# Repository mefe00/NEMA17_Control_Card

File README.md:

# STM32G tabanlı NEMA17 sürücü kartı 

> Bu proje, NEMA17 gibi step motorları alanın az olduğu yerlerde hem kompakt boyut sağlamak hemde kablo karmaşını en aza indirmek için tasarlanmıştır.

## 📋 Özellikler

* MCU: STM32G431CBT6
* Çalışma Gerilimi: 24V
* Haberleşme: CAN/CAN-FD: Kartta iki tane CAN konnektörü vardır. Bu sayede aynı karta veya aynı CAN hattı üzerindeki başka bir kartla haberleşmek için bir konnektöre giriş yapıp diğer konnektörden çıkabilirsiniz ve diğer cihaza giriş yapabilirsiniz. Dikkat: Eğer kartı CAN                   hattının son cihazı ise 60 ohmları buna uygun bir şekilde montajlayın !!!!
              I2C: Eğer motorda redüktör varsa ve kartın arkasındaki encoder kullanılmak istenmezse harici ucuz bir encoder (AS5600) girişi redüktör ucundan alınması içindir. Diğer amacı ise yine bir encoder bağlayıp redüktör boşluğu (backlash) tespiti yapılabilmesi içindir.
              USART: Debug veya direkt haberleşme sağlanabilmesi için. 
* Koruma: 26V seviyesini aşarsa sürücü koruması için TVS diyot
* Encoder: AS5147-P ----> Kartın direkt arkasında bulunur ve pahalı ve kaliteli seçilmesinin sebebi ise redüktör eklenen motorlarda milin daha hızlı dönmesinden dolayı açı verisinin kaçmasını engellemek içindir.
           AS5600   ----> Karta harici bir şekilde girilebilir. Kart üzerinde bunun için harici I2C konnektörü vardır.
* NTC: Kart üzerindeki sıcaklığı tespit etmek için kullanılabilir.
* FAN: NTC'den alınan verilere göre veya manuel soğutma için 24V fan desteği vardır.
* Sürücü: TMC2209 seçilmiştir ama TMC2208 veya pinleri uyuşan başka bir sürücüde kullanılabilir. 

## 📂 Depo İçeriği

* `/Hardware`: KiCAD şematik (`.kicad_sch`) ve PCB (`.kicad_pcb`) tasarım dosyaları.
* `/production`: Üretime hazır Gerber ve Drill dosyaları.
* `/software`: Kartın robot kol eksenlerindeki motorları kontrolü için hazırlanmış gömülü kodu.

## Tavsiyeler

* Güç girişine 50V / 1000uF seviyelerinde bir elektrolit kapasitör eklenmesi.
* Sürücülerin bozulması durumları düşünüldüğü için modül olarak yerleştirilmiştir ve modulün altı boş olduğu için burayada 50V / 220uF seviyelerinde elektrolit kapasitör eklenmesi.
* Daha kararlı bir çalışma olabilmesi için sürücü üzerine soğutucu (heatsink) yerleştirin.
* Daha soğuk bir çalışma için soğutu bloğu buck converter üzerinede yerleştirebilirsiniz.

## Diğer Görseller

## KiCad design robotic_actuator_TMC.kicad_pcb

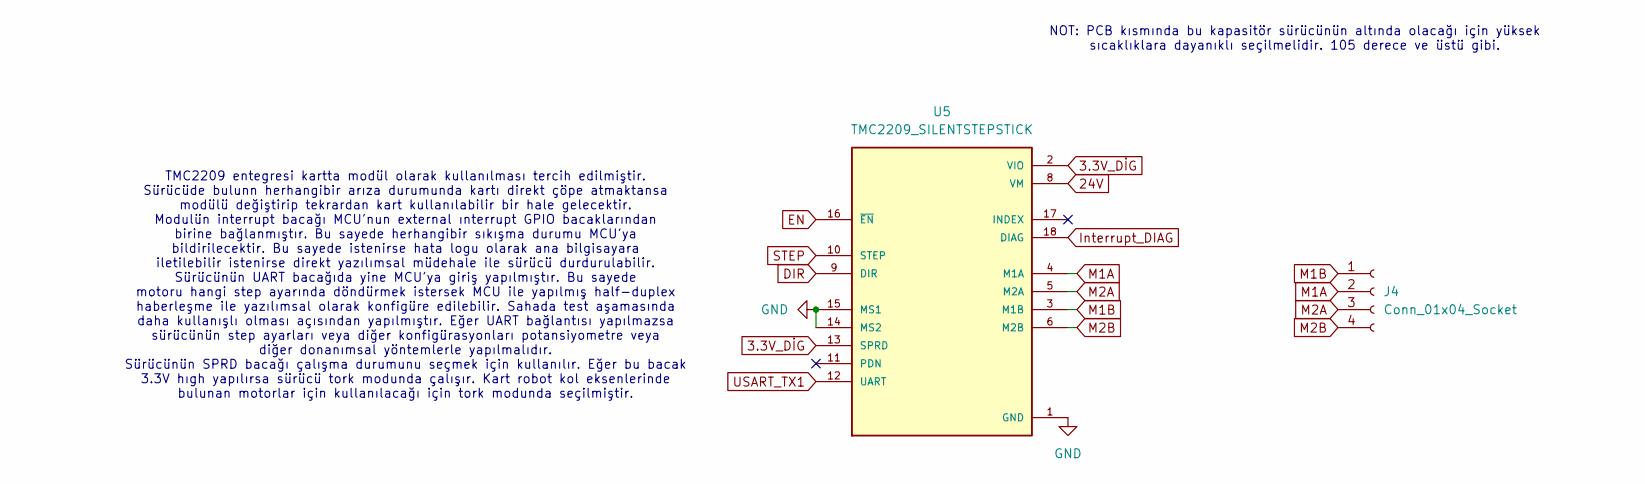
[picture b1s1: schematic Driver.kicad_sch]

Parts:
J4: Conn_01x04_Socket; JST_PH_S4B-PH-K_1x04_P2.00mm_Horizontal
U5: TMC2209_SILENTSTEPSTICK; MODULE_TMC2209_SILENTSTEPSTICK; PARTREV 1.20

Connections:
3.3V_DİG: U5.2 (VIO), U5.13 (SPRD); also elsewhere on the board
24V: U5.8 (VM); also elsewhere on the board
DIR: U5.9 (DIR); also elsewhere on the board
EN: U5.16 (~EN); also elsewhere on the board
GND: U5.1 (GND), U5.7 (GND), U5.14 (MS2), U5.15 (MS1); also elsewhere on the board
Interrupt_DIAG: U5.18 (DIAG); also elsewhere on the board
M1A: J4.2, U5.4 (M1A)
M1B: J4.1, U5.3 (M1B)
M2A: J4.3, U5.5 (M2A)
M2B: J4.4, U5.6 (M2B)
STEP: U5.10 (STEP); also elsewhere on the board
USART_TX1: U5.12 (UART); also elsewhere on the board

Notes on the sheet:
TMC2209 entegresi kartta modül olarak kullanılması tercih edilmiştir. Sürücüde bulunn herhangibir arıza durumunda kartı direkt çöpe atmaktansa modülü değiştirip tekrardan kart kullanılabilir bir hale gelecektir. Modulün interrupt bacağı MCU'nun external ınterrupt GPIO bacaklarından birine bağlanmış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
NOT: PCB kısmında bu kapasitör sürücünün altında olacağı için yüksek sıcaklıklara dayanıklı seçilmelidir. 105 derece ve üstü gibi.

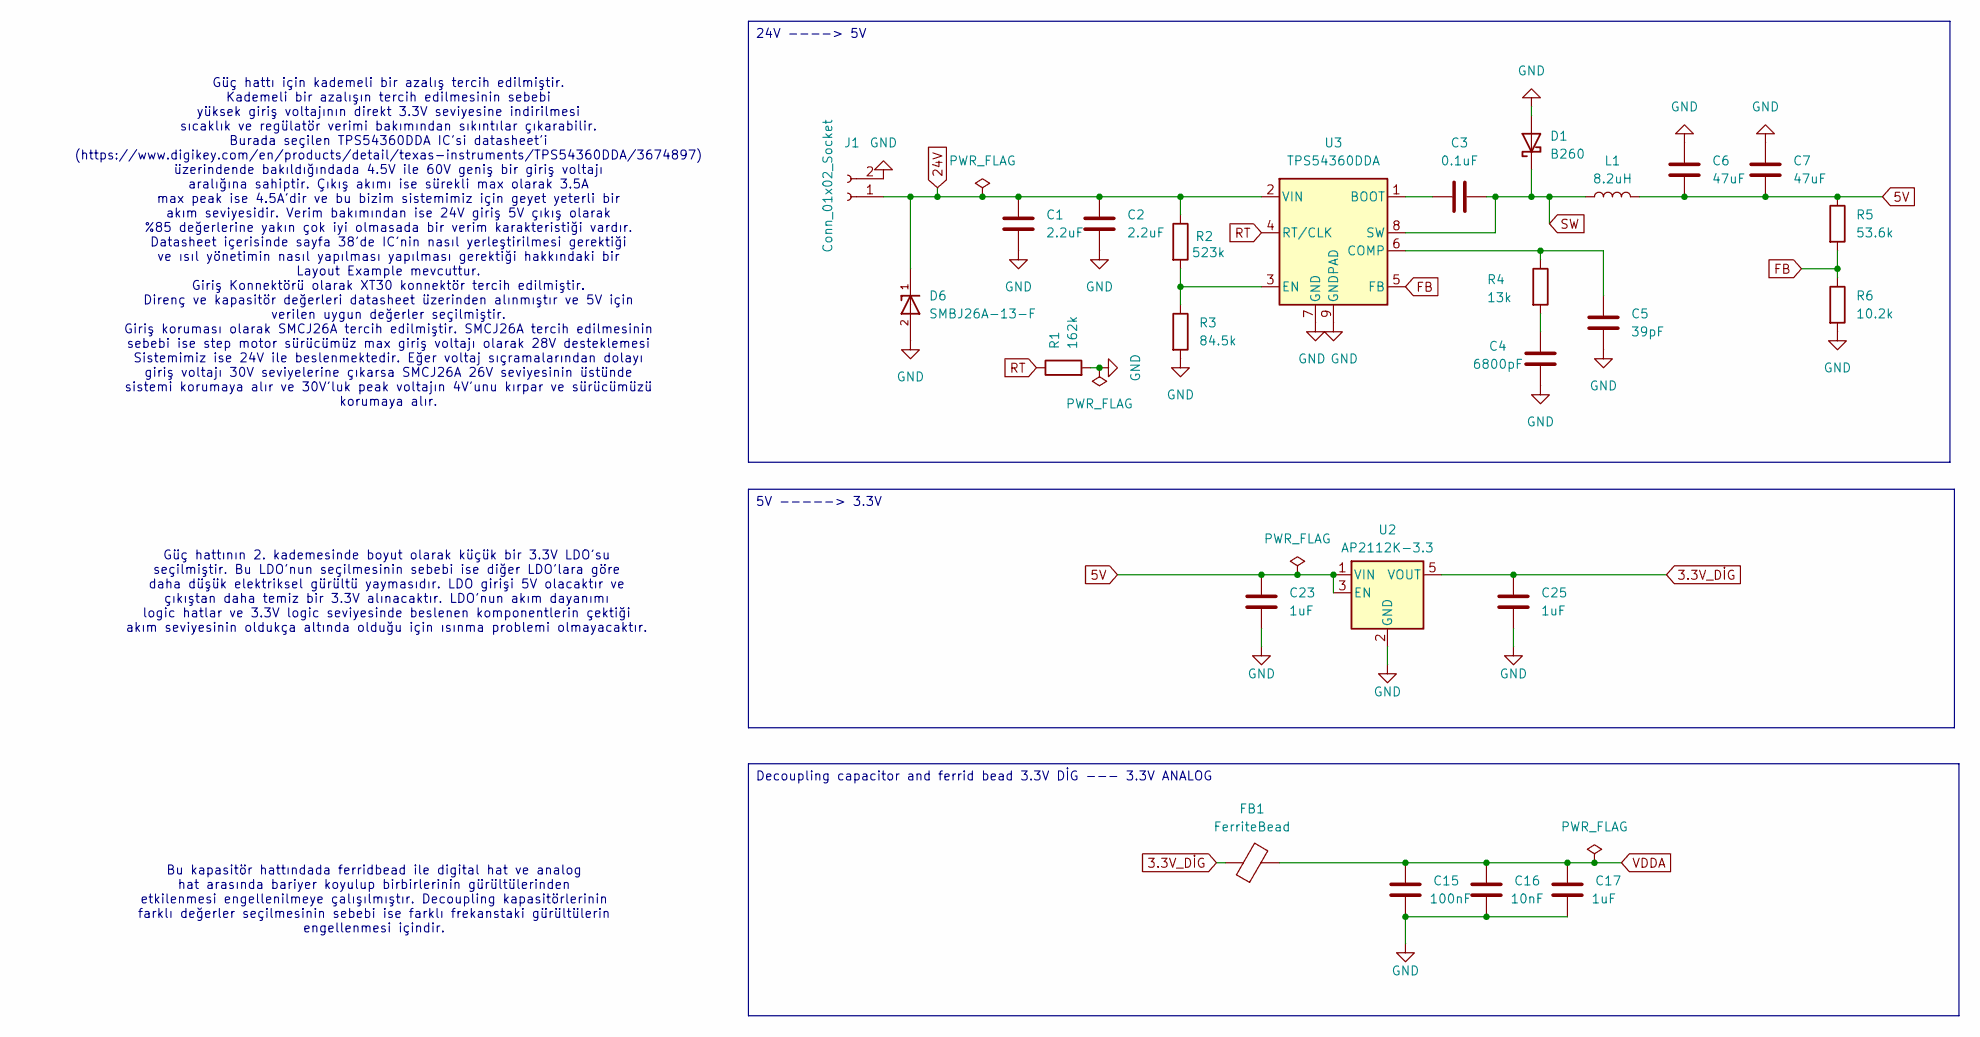
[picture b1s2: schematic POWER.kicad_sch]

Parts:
C1, C2: 2.2uF; C_1206_3216Metric
C3: 0.1uF; C_0603_1608Metric
C4: 6800pF; C_0603_1608Metric
C5: 39pF; C_0603_1608Metric
C6, C7: 47uF; C_0805_2012Metric
C15: 100nF; C_0603_1608Metric
C16: 10nF; C_0603_1608Metric
C17, C23, C25: 1uF; C_0603_1608Metric
D1: B260; D_SMA
D6: SMBJ26A-13-F; D_SMB; PARTREV 20 - 2
FB1: FerriteBead; L_0603_1608Metric
J1: Conn_01x02_Socket; AMASS_XT30U-F_1x02_P5.0mm_Vertical
L1: 8.2uH; L_6.3x6.3_H3
R1: 162k; R_0603_1608Metric
R2: 523k; R_0603_1608Metric
R3: 84.5k; R_0603_1608Metric
R4: 13k; R_0603_1608Metric
R5: 53.6k; R_0603_1608Metric
R6: 10.2k; R_0603_1608Metric
U2: AP2112K-3.3; SOT-23-5
U3: TPS54360DDA; TI_SO-PowerPAD-8_ThermalVias

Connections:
3.3V_DİG: C25.1, FB1.1, U2.5 (VOUT); also elsewhere on the board
5V: C6.1, C7.1, C23.1, L1.2, R5.1, U2.1 (VIN), U2.3 (EN); also elsewhere on the board
24V: C1.1, C2.1, D6.1, J1.1, R2.1, U3.2 (VIN); also elsewhere on the board
FB: R5.2, R6.1, U3.5 (FB)
GND: C1.2, C2.2, C4.1, C5.1, C6.2, C7.2, C15.2, C16.2, C17.2, C23.2, C25.2, D1.2 (A), D6.2, J1.2, R1.2, R3.2, R6.2, U2.2 (GND), U3.7 (GND), U3.9 (GNDPAD); also elsewhere on the board
unnamed: C4.2, R4.2
unnamed: C3.1, U3.1 (BOOT)
unnamed: C5.2, R4.1, U3.6 (COMP)
unnamed: R2.2, R3.1, U3.3 (EN)
RT: R1.1, U3.4 (RT/CLK)
SW: C3.2, D1.1 (K), L1.1, U3.8 (SW)
VDDA: C15.1, C16.1, C17.1, FB1.2; also elsewhere on the board

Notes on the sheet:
Güç hattının 2. kademesinde boyut olarak küçük bir 3.3V LDO'su seçilmiştir. Bu LDO'nun seçilmesinin sebebi ise diğer LDO'lara göre daha düşük elektriksel gürültü yaymasıdır. LDO girişi 5V olacaktır ve çıkıştan daha temiz bir 3.3V alınacaktır. LDO'nun akım dayanımı logic hatlar ve 3.3V logic seviyes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
Bu kapasitör hattındada ferridbead ile digital hat ve analog hat arasında bariyer koyulup birbirlerinin gürültülerinden etkilenmesi engellenilmeye çalışılmıştır. Decoupling kapasitörlerinin farklı değerler seçilmesinin sebebi ise farklı frekanstaki gürültülerin engellenmesi içindir.
Güç hattı için kademeli bir azalış tercih edilmiştir. Kademeli bir azalışın tercih edilmesinin sebebi yüksek giriş voltajının direkt 3.3V seviyesine indirilmesi sıcaklık ve regülatör verimi bakımından sıkıntılar çıkarabilir. Burada seçilen TPS54360DDA IC'si datasheet'i (https://www.digikey.com/en/p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
Decoupling capacitor and ferrid bead 3.3V DİG --- 3.3V ANALOG
5V -----> 3.3V
24V ----> 5V

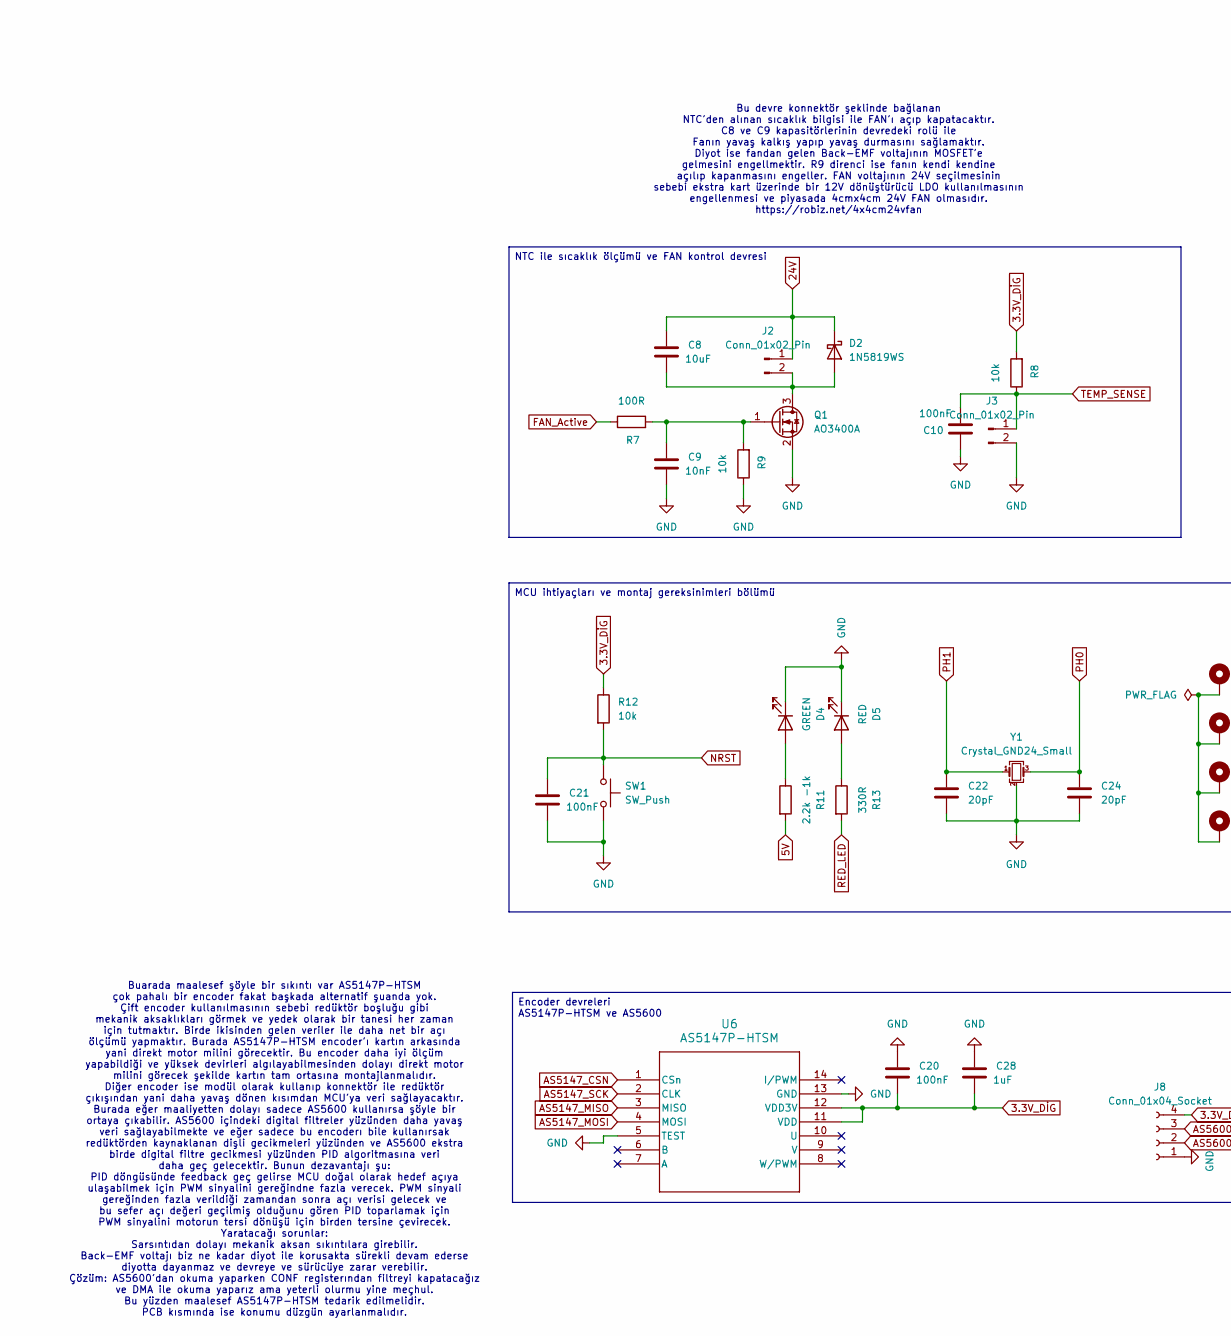
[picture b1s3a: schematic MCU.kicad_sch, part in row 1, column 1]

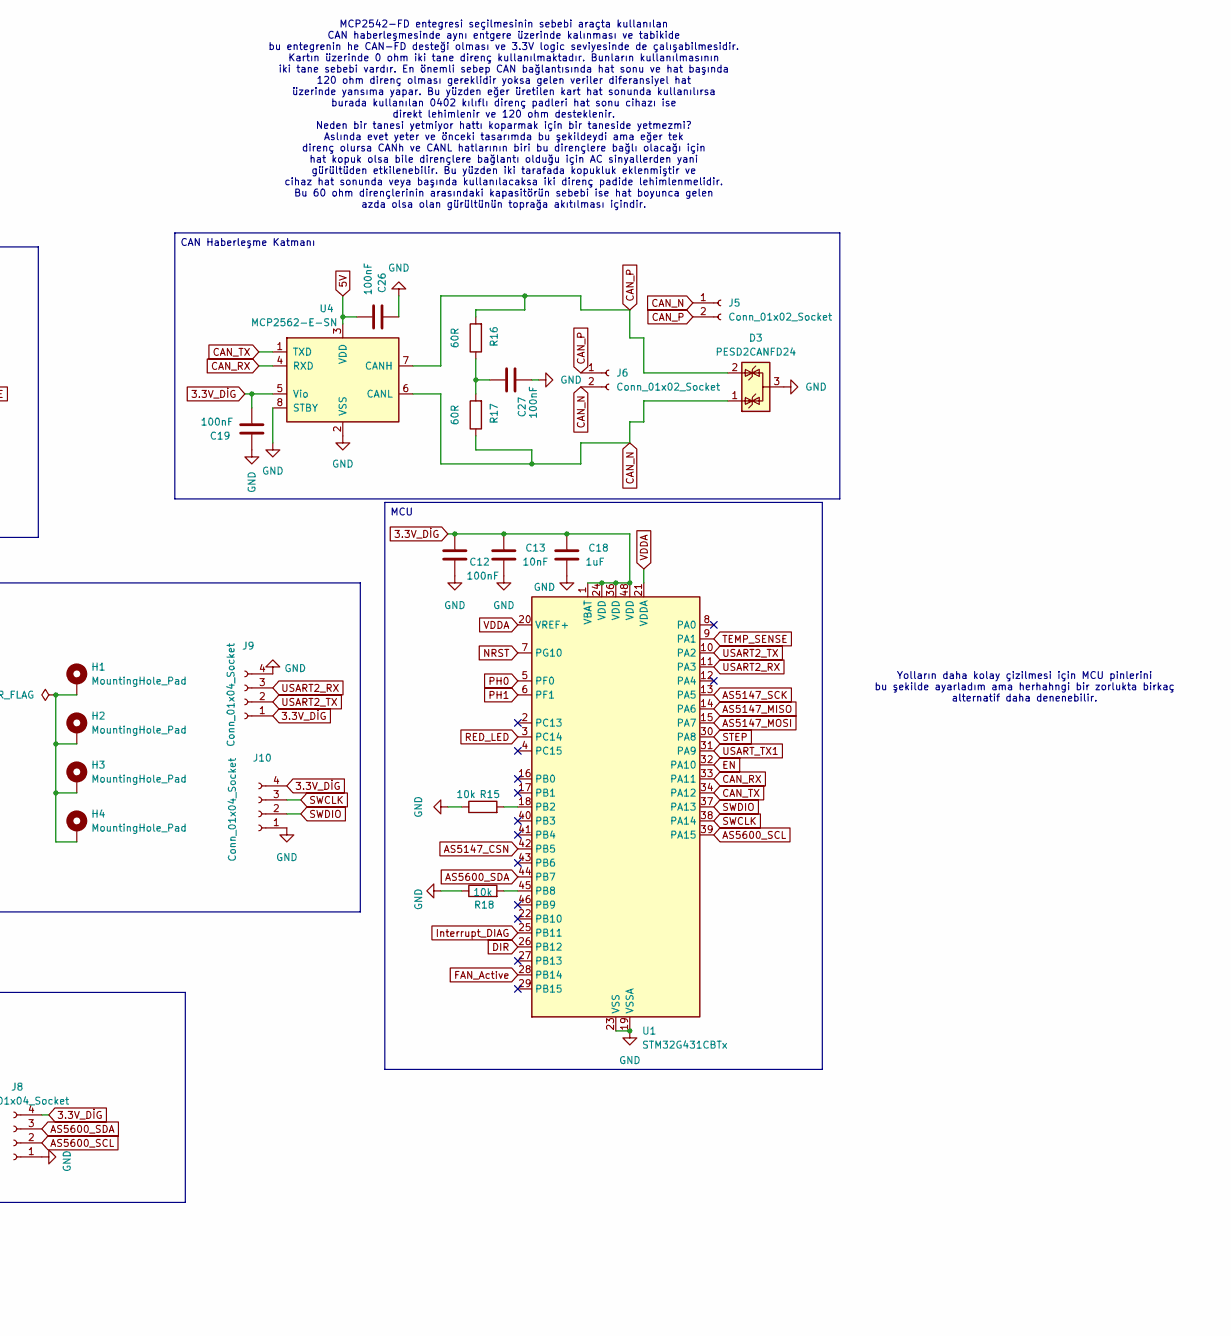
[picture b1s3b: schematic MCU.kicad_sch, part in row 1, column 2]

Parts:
C8: 10uF; C_0603_1608Metric
C9, C13: 10nF; C_0603_1608Metric
C10, C12, C19, C20, C21, C26, C27: 100nF; C_0603_1608Metric
C18, C28: 1uF; C_0603_1608Metric
C22, C24: 20pF; C_0603_1608Metric
D2: 1N5819WS; D_SOD-323
D3: PESD2CANFD24; DIO_PESD2CAN_215
D4: GREEN; LED_0603_1608Metric
D5: RED; LED_0603_1608Metric
H1, H2, H3, H4: MountingHole_Pad; MountingHole_3.5mm
J2, J3: Conn_01x02_Pin; PinHeader_1x02_P2.54mm_Vertical
J5, J6: Conn_01x02_Socket; JST_GH_SM02B-GHS-TB_1x02-1MP_P1.25mm_Horizontal
J8, J9, J10: Conn_01x04_Socket; JST_GH_SM04B-GHS-TB_1x04-1MP_P1.25mm_Horizontal
Q1: AO3400A; SOT-23
R7: 100R; R_0603_1608Metric
R8, R9, R12, R15, R18: 10k; R_0603_1608Metric
R11: 2.2k -1k; R_0603_1608Metric
R13: 330R; R_0603_1608Metric
R16, R17: 60R; R_0603_1608Metric
SW1: SW_Push; SW_Push_1P1T_NO_CK_KMR2
U1: STM32G431CBTx; LQFP-48_7x7mm_P0.5mm
U4: MCP2562-E-SN; SOIC-8_3.9x4.9mm_P1.27mm
U6: AS5147P-HTSM; TSSOP-14_AMS
Y1: Crystal_GND24_Small; Crystal_SMD_3225-4Pin_3.2x2.5mm

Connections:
3.3V_DİG: C12.1, C13.1, C18.1, C19.2, C20.2, C28.2, J8.4, J9.1, J10.4, R8.2, R12.1, U1.1 (VBAT), U1.24 (VDD), U1.36 (VDD), U1.48 (VDD), U4.5 (Vio), U6.11 (VDD), U6.12 (VDD3V); also elsewhere on the board
5V: C26.2, R11.2, U4.3 (VDD); also elsewhere on the board
24V: C8.1, D2.1 (K), J2.1; also elsewhere on the board
AS5147_CSN: U1.42 (PB5), U6.1 (CSn)
AS5147_MISO: U1.14 (PA6), U6.3 (MISO)
AS5147_MOSI: U1.15 (PA7), U6.4 (MOSI)
AS5147_SCK: U1.13 (PA5), U6.2 (CLK)
AS5600_SCL: J8.2, U1.39 (PA15)
AS5600_SDA: J8.3, U1.44 (PB7)
CAN_N: D3.1 (K), J5.1, J6.2, R17.1, U4.6 (CANL)
CAN_P: D3.2 (K), J5.2, J6.1, R16.2, U4.7 (CANH)
CAN_RX: U1.33 (PA11), U4.4 (RXD)
CAN_TX: U1.34 (PA12), U4.1 (TXD)
DIR: U1.26 (PB12); also elsewhere on the board
EN: U1.32 (PA10); also elsewhere on the board
FAN_Active: R7.1, U1.28 (PB14)
GND: C9.2, C10.2, C12.2, C13.2, C18.2, C19.1, C20.1, C21.2, C22.2, C24.2, C26.1, C27.2, C28.1, D3.3 (A), D4.1 (K), D5.1 (K), J3.2, J8.1, J9.4, J10.1, Q1.2 (S), R9.1, R15.1, R18.1, SW1.2, U1.19 (VSSA), U1.23 (VSS), U1.35 (VSS), U1.47 (VSS), U4.2 (VSS), U4.8 (STBY), U6.5 (TEST), U6.13 (GND), Y1.2 (G), Y1.4 (G); also elsewhere on the board
Interrupt_DIAG: U1.25 (PB11); also elsewhere on the board
NRST: C21.1, R12.2, SW1.1, U1.7 (PG10)
unnamed: C27.1, R16.1, R17.2
unnamed: C8.2, D2.2 (A), J2.2, Q1.3 (D)
unnamed: D4.2 (A), R11.1
unnamed: D5.2 (A), R13.1
unnamed: C9.1, Q1.1 (G), R7.2, R9.2
unnamed: R15.2, U1.18 (PB2)
unnamed: R18.2, U1.45 (PB8)
PH0: C24.1, U1.5 (PF0), Y1.3
PH1: C22.1, U1.6 (PF1), Y1.1
RED_LED: R13.2, U1.3 (PC14)
STEP: U1.30 (PA8); also elsewhere on the board
SWCLK: J10.3, U1.38 (PA14)
SWDIO: J10.2, U1.37 (PA13)
TEMP_SENSE: C10.1, J3.1, R8.1, U1.9 (PA1)
USART2_RX: J9.3, U1.11 (PA3)
USART2_TX: J9.2, U1.10 (PA2)
USART_TX1: U1.31 (PA9); also elsewhere on the board
VDDA: U1.20 (VREF+), U1.21 (VDDA); also elsewhere on the board

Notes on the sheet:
Buarada maalesef şöyle bir sıkıntı var AS5147P-HTSM çok pahalı bir encoder fakat başkada alternatif şuanda yok. Çift encoder kullanılmasının sebebi redüktör boşluğu gibi mekanik aksaklıkları görmek ve yedek olarak bir tanesi her zaman için tutmaktır. Birde ikisinden gelen veriler ile daha net bir a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
Bu devre konnektör şeklinde bağlanan NTC'den alınan sıcaklık bilgisi ile FAN'ı açıp kapatacaktır. C8 ve C9 kapasitörlerinin devredeki rolü ile Fanın yavaş kalkış yapıp yavaş durmasını sağlamaktır. Diyot ise fandan gelen Back-EMF voltajının MOSFET'e gelmesini engellmektir. R9 direnci ise fanın kendi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
MCP2542-FD entegresi seçilmesinin sebebi araçta kullanılan CAN haberleşmesinde aynı entgere üzerinde kalınması ve tabikide bu entegrenin he CAN-FD desteği olması ve 3.3V logic seviyesinde de çalışabilmesidir. Kartın üzerinde 0 ohm iki tane direnç kullanılmaktadır. Bunların kullanılmasının iki tane 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
Yolların daha kolay çizilmesi için MCU pinlerini bu şekilde ayarladım ama herhahngi bir zorlukta birkaç alternatif daha denenebilir.
MCU
MCU ihtiyaçları ve montaj gereksinimleri bölümü
CAN Haberleşme Katmanı
NTC ile sıcaklık ölçümü ve FAN kontrol devresi
Encoder devreleri AS5147P-HTSM ve AS5600

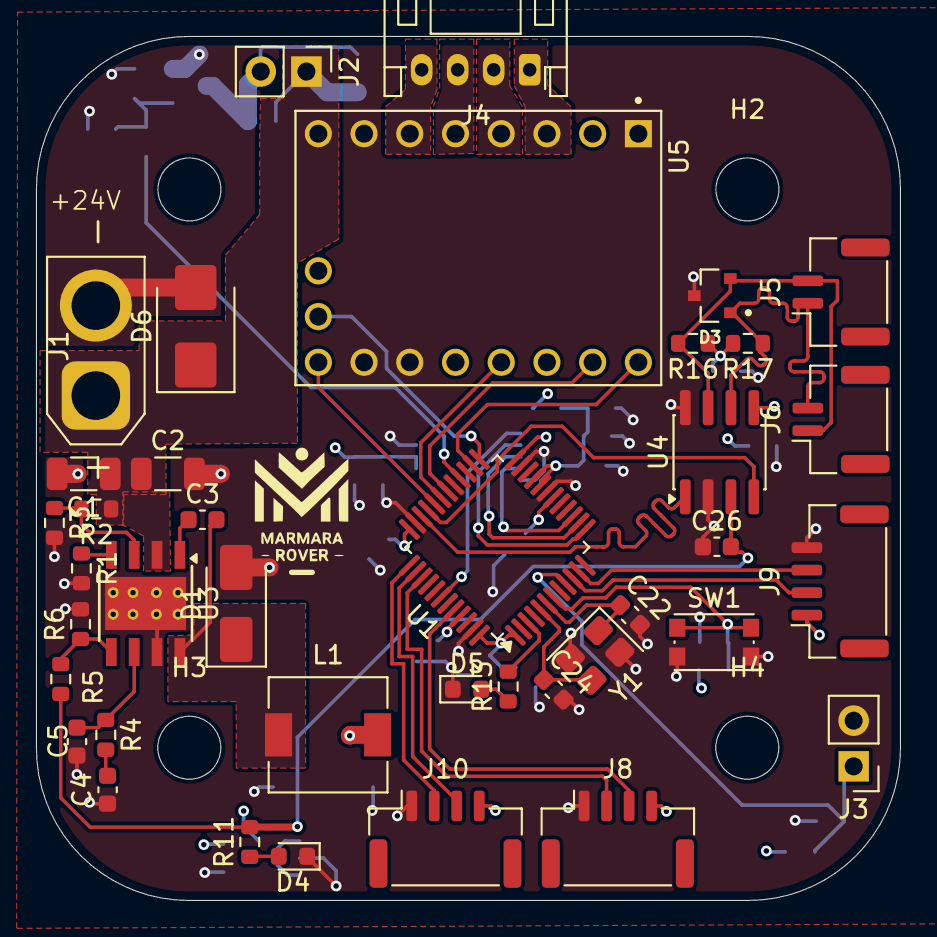
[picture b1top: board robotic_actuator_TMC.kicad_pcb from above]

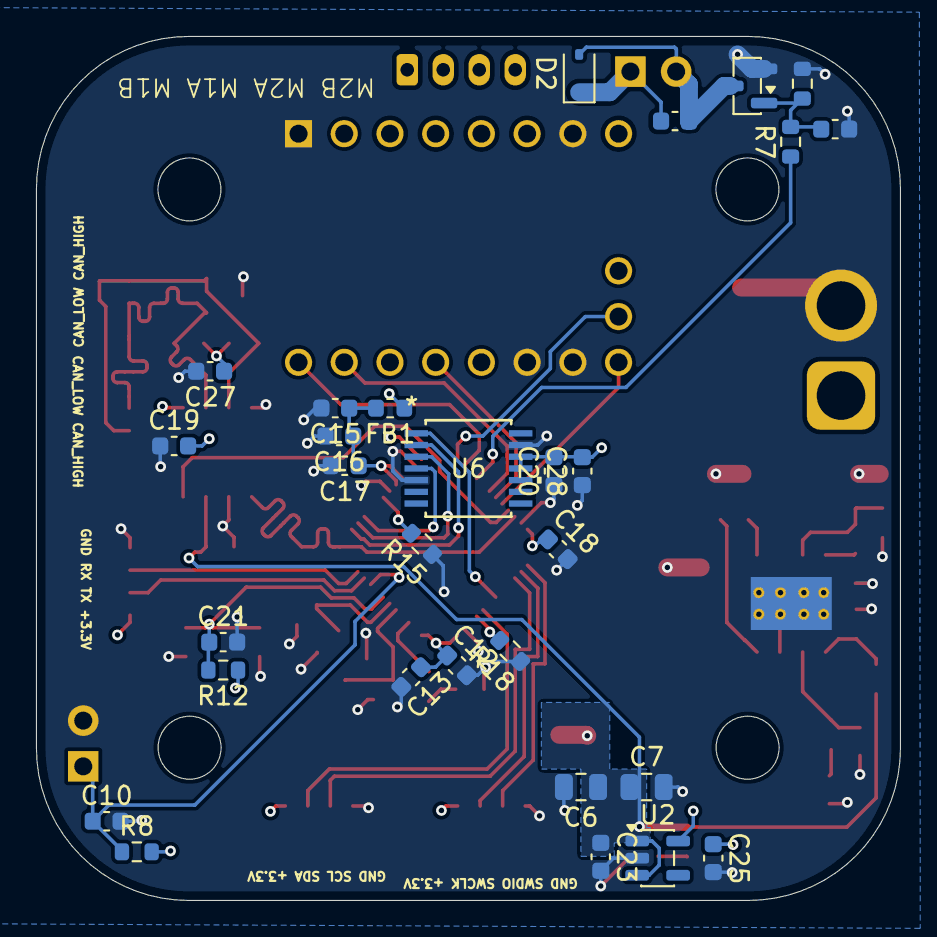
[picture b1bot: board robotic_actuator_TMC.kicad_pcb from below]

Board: 4 copper layers, 48.0 x 48.0 mm, 73 parts (29 on the bottom side), 48 nets.

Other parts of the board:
-: LOGO; Logo

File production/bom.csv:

Designator,Footprint,Quantity,Value,LCSC Part #,Description
"C1, C2",1206,2,2.2uF,C50254,"Ceramic Capacitor 2.2uF 50V X7R 10%
"
"C10, C12, C15, C19, C20, C21, C26, C27",603,8,100nF,C14663,
"C13, C16, C9",603,3,10nF,C100042 ,Soft-Start (SS/TR) kapasitörü.
"C17, C18, C23, C25, C28",603,5,1uF,C15849,
"C22, C24",603,2,20pF,C1648 ,
C3,603,1,0.1uF,C53084455,"C3 giriş filtresi, C8 ise BOOT kapasitörü 
"
C4,603,1,6800pF,C107097,"Kompanzasyon (COMP) ağı kapasitörü.
"
C5,603,1,39pF,C107049,Kompanzasyon (COMP) ağı yüksek frekans kapasitörü (NP0/C0G dielektrik).
"C6, C7",805,2,47uF,C6119904,"5V çıkış hattı filtre kapasitörleri. 5V için 10V voltaj dayanımı yeterlidir.
"
C8,603,1,10uF,C53084455,
D1,D_SMA,1,B260,C109094,"60V 2A Schottky Diyot. (MCU ve sensörler için 2A fazlasıyla yeterli)
"
D2,D_SOD-323,1,1N5819WS,C191023,
D3,DIO_PESD2CAN_215,1,PESD2CANFD24,C5278878 ,
D4,603,1,GREEN,C2986048,
D5,603,1,RED,C183848,
D6,D_SMB,1,SMBJ26A-13-F,C135062,TVS Diode Unidirectional 26V WM 600W
FB1,603,1,FerriteBead,C14709,
J1,AMASS_XT30U-F_1x02_P5.0mm_Vertical,1,Conn_01x02_Socket,,
"J10, J8, J9",JST_GH_SM04B-GHS-TB_1x04-1MP_P1.25mm_Horizontal,3,Conn_01x04_Socket,C189895,
"J2, J3",PinHeader_1x02_P2.54mm_Vertical,2,Conn_01x02_Pin,,
J4,JST_PH_S4B-PH-K_1x04_P2.00mm_Horizontal,1,Conn_01x04_Socket,,
"J5, J6",JST_GH_SM02B-GHS-TB_1x02-1MP_P1.25mm_Horizontal,2,Conn_01x02_Socket,C189893,
L1,L_6.3x6.3_H3,1,8.2uH,C167222,"6x6x2.8mm SMD Bobin (Sunlord). Doyuma ulaşma akımı 2.5A, bu sistem için ideal.

"
Q1,SOT-23,1,AO3400A,C20917 ,
R1,603,1,162k,C2998114,EN (Enable) pini voltaj bölücü alt direnci.
R11,603,1,2.2k -1k,C22548,
"R12, R15, R18, R8, R9",603,5,10k,C98220 ,
R13,603,1,330R,C105881 ,
"R16, R17",603,2,60R,C85834 ,
R2,603,1,523k,C5126197,"EN (Enable) pini voltaj bölücü üst direnci.
"
R3,603,1,84.5k,C855976,RT/CLK frekans ayar direnci.
R4,603,1,13k,C137796,Kompanzasyon (COMP) ağı direnci.
R5,603,1,53.6k,C2930115,"Feedback (FB) üst direnci (Hassas 5V çıkış için %1 tolerans).
"
R6,603,1,10.2k,C22772 ,"Feedback (FB) alt direnci (Hassas 5V çıkış için %1 tolerans).
"
R7,603,1,100R,C105588 ,
SW1,SW_Push_1P1T_NO_CK_KMR2,1,SW_Push,C99271,
U1,LQFP-48_7x7mm_P0.5mm,1,STM32G431CBT6,C529355,MCU 
U2,SOT-23-5,1,AP2112K-3.3,C51118 ,3.3V LDO
U3,TI_SO-PowerPAD-8_ThermalVias,1,TPS54360DDA,C465733,"60V, 3.5A Step-Down Converter"
U4,SOIC-8_3.9x4.9mm_P1.27mm,1,MCP2562-E-SN,C53609 ,CAN entegresi
U5,MODULE_TMC2209_SILENTSTEPSTICK,1,TMC2209_SILENTSTEPSTICK,,
U6,TSSOP-14_AMS,1,AS5147P-HTSM,C22426928 ,Encoder
Y1,Crystal_SMD_3225-4Pin_3.2x2.5mm,1,Crystal_GND24_Small,C7275084,Kristal
